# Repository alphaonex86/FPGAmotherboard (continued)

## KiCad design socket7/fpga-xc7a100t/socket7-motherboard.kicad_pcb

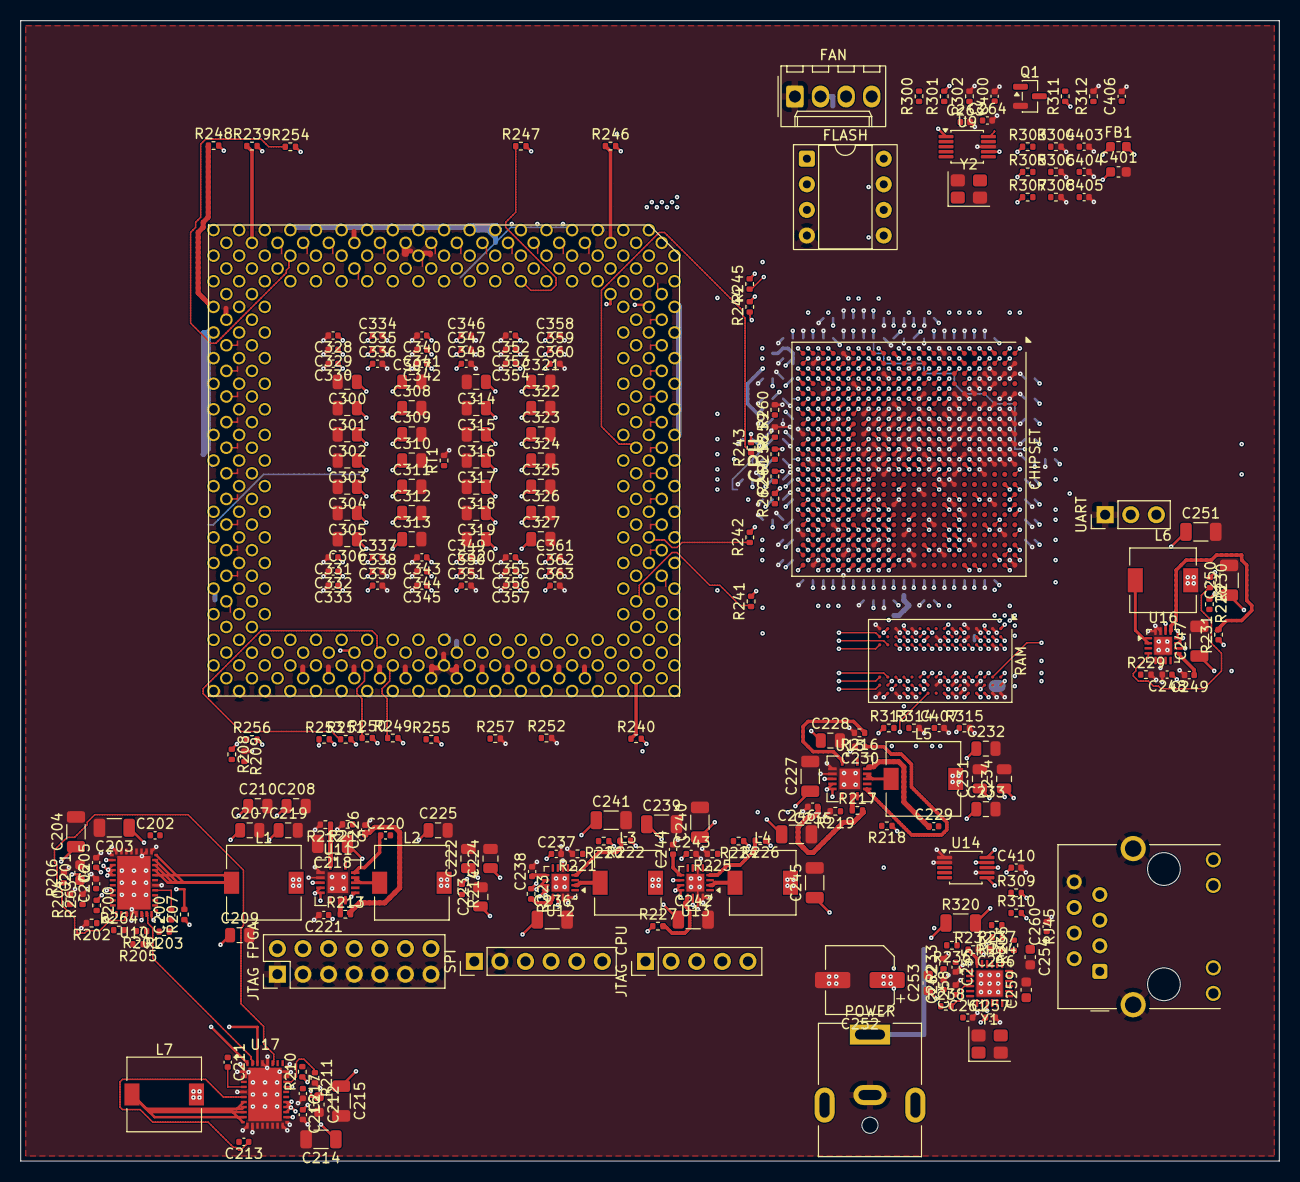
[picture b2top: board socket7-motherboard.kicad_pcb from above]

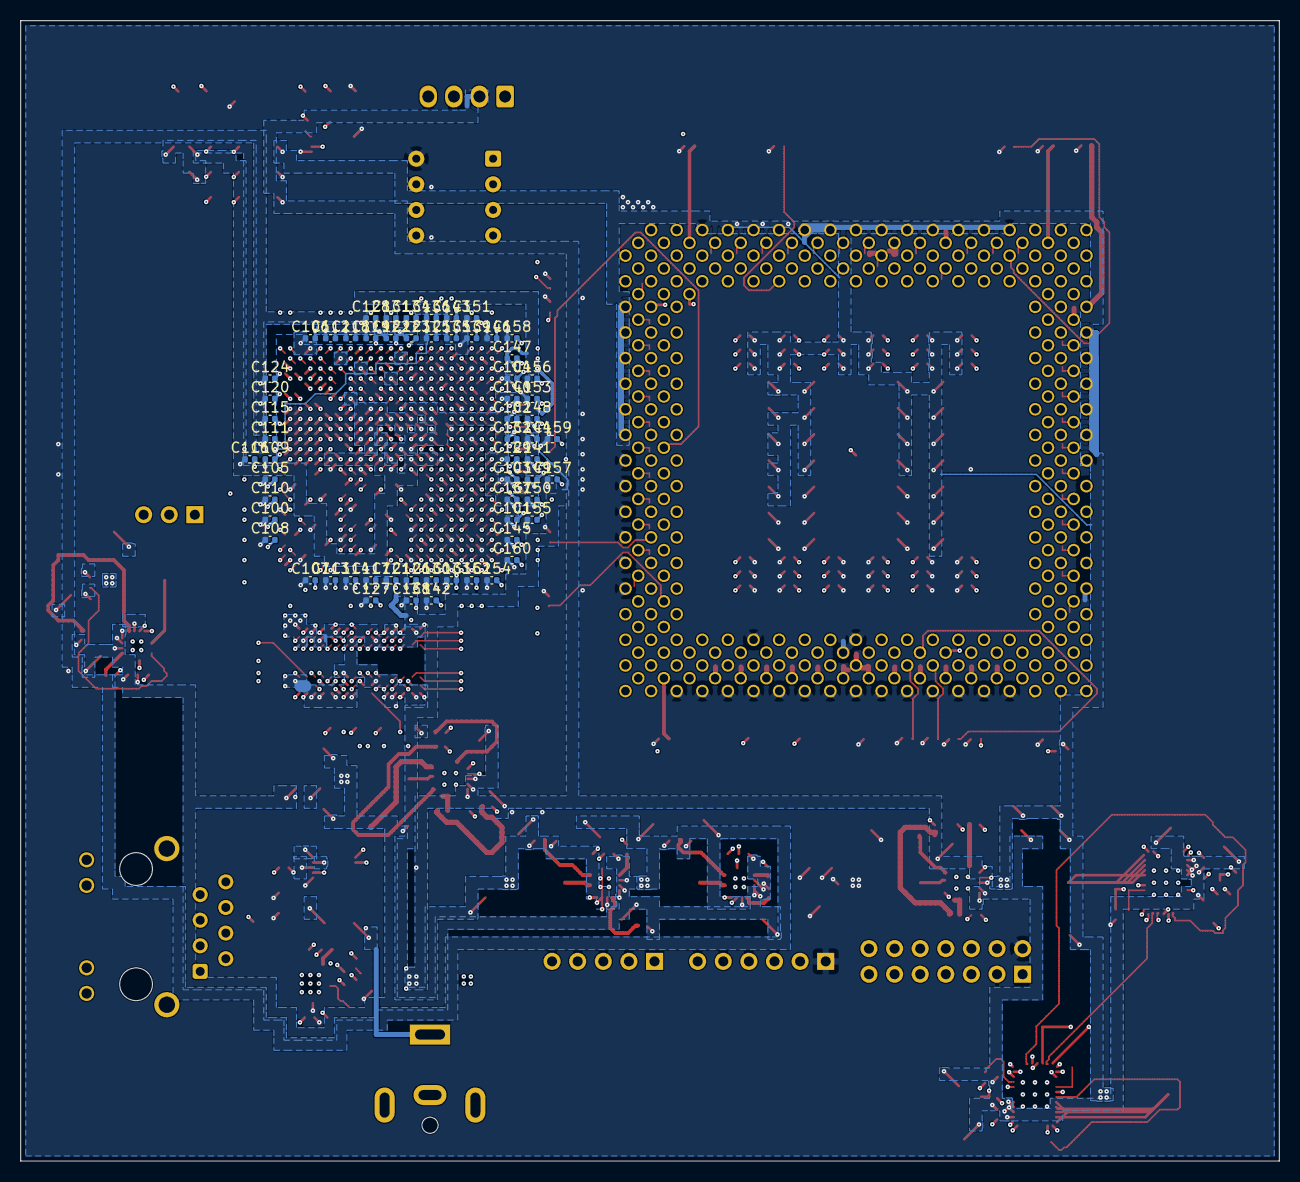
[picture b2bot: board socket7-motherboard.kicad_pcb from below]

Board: 8 copper layers, 124.8 x 113.1 mm, 313 parts (61 on the bottom side), 311 nets.

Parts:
C100, C101, C102, C103, C104, C105, C106, C107, C108, C109, C110, C111, C112, C113, C114, C115, C116, C117, C118, C119, C120, C121, C122, C123, C124, C125, C126, C127, C128, C129, C130, C131, C132, C133, C134, C135, C136, C137, C138, C139, C140, C141, C142, C143, C144, C145, C146, C147, C148, C149, C150, C151, C152, C153, C154, C155, C156, C157, C158, C159, C160: 470nF; C_0402_1005Metric
C200, C211: 1uF 16V X6S; C_0402_1005Metric
C201, C212: 4.7uF 16V X5R; C_0603_1608Metric
C202, C213: 100nF 16V X5R; C_0402_1005Metric
C203, C204, C214, C215, C218, C227, C236, C239, C240, C241, C242, C245, C246, C247, C250, C251: 22uF 25V X5R; C_1206_3216Metric
C205, C216, C221, C230, C403, C404, C405, C406: 10nF 50V X7R; C_0402_1005Metric
C206, C217: 1uF 25V X5R; C_0402_1005Metric
C207, C208, C209, C210, C222, C223, C224, C225: 47uF 6.3V X5R; C_0805_2012Metric
C219, C228: 4.7uF 25V X7R; C_0805_2012Metric
C220, C229, C237, C243, C248, C255, C256, C257, C260, C407, C410: 100nF 16V X7R; C_0402_1005Metric
C226, C235: 8.2nF 50V X7R; C_0402_1005Metric
C231, C232, C233, C234: 47uF 10V X5R; C_0805_2012Metric
C238, C244, C249: 3.3nF 50V X7R; C_0402_1005Metric
C252: 100uF 25V; CP_Elec_6.3x7.7
C253: 600R@100MHz bead; L_0603_1608Metric
C254: 10uF 10V X5R; C_0603_1608Metric
C258: 470pF 50V C0G; C_0402_1005Metric
C259: 1uF 16V X7R; C_0603_1608Metric
C261, C262: 15pF 50V C0G; C_0402_1005Metric
C263, C264: 4pF 50V C0G; C_0402_1005Metric
C300, C301, C302, C303, C304, C305, C306, C307, C308, C309, C310, C311, C312, C313, C314, C315, C316, C317, C318, C319, C320, C321, C322, C323, C324, C325, C326, C327: 22uF; C_0805_2012Metric
C328, C329, C330, C331, C332, C333, C334, C335, C336, C337, C338, C339, C340, C341, C342, C343, C344, C345, C346, C347, C348, C349, C350, C351, C352, C353, C354, C355, C356, C357, C358, C359, C360, C361, C362, C363: 100nF; C_0402_1005Metric
C400: 1nF 50V C0G; C_0402_1005Metric
C401: 470nF 50V X7R; C_0603_1608Metric
FB1: 600R@100MHz bead; L_0603_1608Metric
J1: HR911105A; RJ45_Hanrun_HR911105A_Horizontal
J2: SPI ISP; PinHeader_1x06_P2.54mm_Vertical
J3: PJ-063AH 12V; BarrelJack_CUI_PJ-063AH_Horizontal
J4: UART; PinHeader_1x03_P2.54mm_Vertical
J5: FPGA JTAG; PinHeader_2x07_P2.54mm_Vertical
J6: CPU JTAG; PinHeader_1x05_P2.54mm_Vertical
J7: fan 4-pin 1GND 2+12V 3TACH 4PWM; Molex_KK-254_AE-6410-04A_1x04_P2.54mm_Vertical
L1: VCC2 out; L_7.3x7.3_H4.5
L2: 3V3 out; L_7.3x7.3_H4.5
L3: 1V0 out; L_6.3x6.3_H3
L4: 1V8 out; L_6.3x6.3_H3
L5: 5V out; L_7.3x7.3_H4.5
L6: 1V35 out; L_6.3x6.3_H3
L7: VCC2 ph2 out; L_7.3x7.3_H4.5
Q1: BSS138; SOT-23
R200, R210: 10R 1%; R_0402_1005Metric
R201, R202, R205: 21.5k 1%; R_0402_1005Metric
R203: 110k 1%; R_0402_1005Metric
R204: 56.2k 1%; R_0402_1005Metric
R206: 4.64k 1%; R_0402_1005Metric
R207, R215, R219, R221, R225, R229, R233, R252, R257, R301, R302, R303, R305, R309, R310, R311: 10k 1%; R_0402_1005Metric
R208: 866R 1%; R_0402_1005Metric
R209: 0R; R_0402_1005Metric
R211: 17.8k 1%; R_0402_1005Metric
R212, R216, R222, R223, R226, R227, R230, R231: 100k 1%; R_0402_1005Metric
R213, R217, R300: 1.69k 1%; R_0402_1005Metric
R214: 31.6k 1%; R_0402_1005Metric
R218: 52.3k 1%; R_0402_1005Metric
R220, R308: 2.49k 1%; R_0402_1005Metric
R224: 12.4k 1%; R_0402_1005Metric
R228: 6.81k 1%; R_0402_1005Metric
R232: 12.1k 1%; R_0402_1005Metric
R234, R235, R236, R237: 49.9 1%; R_0402_1005Metric
R238, R263: 500R 1%; R_0402_1005Metric
R239, R248, R249, R251, R256: 8.2k 1%; R_0402_1005Metric
R240, R241, R242, R243, R244, R245, R246, R247, R250, R253, R254, R255: 4.7k 1%; R_0402_1005Metric
R258, R259, R260, R264, R313, R314: 1k 1%; R_0402_1005Metric
R261, R262, R304, R306, R312: 4.02k 1%; R_0402_1005Metric
R307: 30.9k 1%; R_0402_1005Metric
R315: 240R 1%; R_0402_1005Metric
R320: 10mR 1% 1W; R_1206_3216Metric
RT1: 10k NTC 1% B3380; R_0402_1005Metric
U2: XC7A100T-2FGG484I; Xilinx_FGG484
U3: MT41K128M16JT-125; FBGA-96_8x14mm_Layout9x16_P0.8mm
U7: LAN8720A-CP-TR; QFN-24-1EP_4x4mm_P0.5mm_EP2.6x2.6mm
U8: W25Q64JVDAIQ (DIP-8, socketed); DIP-8_W7.62mm_Socket
U9: SI5351A-B-GTR; MSOP-10_3x3mm_P0.5mm
U10: TPS546B24ARVFR VCC2; Texas_RVF0040A_LQFN-CLIP-40_5x7mm_P0.5mm
U11: TPS54620RGYR 3V3; Texas_S-PVQFN-N14
U12: TPS62130RGTR 1V0; QFN-16-1EP_3x3mm_P0.5mm_EP1.75x1.75mm
U13: TPS62130RGTR 1V8; QFN-16-1EP_3x3mm_P0.5mm_EP1.75x1.75mm
U14: INA226AIDGSR; MSOP-10_3x3mm_P0.5mm
U15: TPS54620RGYR 5V; Texas_S-PVQFN-N14
U16: TPS62130RGTR 1V35; QFN-16-1EP_3x3mm_P0.5mm_EP1.75x1.75mm
U17: TPS546B24ARVFR VCC2 ph2; Texas_RVF0040A_LQFN-CLIP-40_5x7mm_P0.5mm
XU1: Socket 7 ZIF 321p; Socket7_P55C_296
Y1, Y2: 25MHz; Crystal_SMD_3225-4Pin_3.2x2.5mm

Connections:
+1V0: C115.1, C119.1, C120.1, C123.1, C124.1, C128.1, C129.1, C131.1, C135.1, C137.1, C139.1, C140.1, C143.1, C147.1, C148.1, C149.1, C153.1, C239.1, C240.1, C241.1, L3.2, R220.1, R222.1, U2.H8, U2.H10, U2.J7, U2.J9, U2.J11, U2.K8, U2.L7, U2.L11, U2.M8, U2.N7, U2.N11, U2.P8, U2.P10, U2.R7, U2.R9, U2.T8, U2.T10, U12.14
+1V8: C109.1, C116.1, C126.1, C132.1, C141.1, C144.1, C245.1, C246.1, FB1.1, L4.2, R224.1, R226.1, U2.E12, U2.H12, U2.K12, U2.M12, U2.P12, U2.R11, U13.14
+1V8_ADC: C125.1, C401.1, FB1.2, U2.K10
+1V35: C106.1, C112.1, C118.1, C122.1, C134.1, C136.1, C250.1, C251.1, L6.2, R228.1, R230.1, R313.1, U2.C1, U2.F2, U2.H6, U2.J3, U2.M4, U2.N1, U3.A1, U3.A8, U3.B2, U3.C1, U3.C9, U3.D2, U3.D9, U3.E9, U3.F1, U3.G7, U3.H2, U3.H9, U3.K2, U3.K8, U3.N1, U3.N9, U3.R1, U3.R9, U16.14
+3V3: C100.1, C101.1, C102.1, C103.1, C104.1, C105.1, C107.1, C108.1, C110.1, C111.1, C113.1, C114.1, C117.1, C121.1, C127.1, C130.1, C133.1, C138.1, C142.1, C145.1, C146.1, C150.1, C151.1, C152.1, C154.1, C155.1, C156.1, C157.1, C158.1, C159.1, C160.1, C222.1, C223.1, C224.1, C225.1, C253.1, C257.1, C311.1, C312.1, C313.1, C318.1, C319.1, C320.1, C326.1, C327.1, C331.1, C332.1, C333.1, C337.1, C338.1, C339.1, C343.1, C344.1, C345.1, C349.1, C350.1, C351.1, C355.1, C356.1, C357.1, C361.1, C362.1, C363.1, C410.1, J2.1, J5.2, L2.2, R207.1, R214.1, R239.2, R240.2, R241.2, R242.2, R243.2, R244.2, R245.2, R246.2, R247.2, R248.2, R249.2, R250.2, R251.2, R253.2, R254.2, R255.2, R256.2, R258.2, R261.2, R262.2, R301.2, R305.1, R309.2, R310.2, R311.1, U2.A17, U2.AA7, U2.AA17, U2.AB4, U2.AB14, U2.B14, U2.C21, U2.D18, U2.E15, U2.F12, U2.F22, U2.G19, U2.H16, U2.J13, U2.K20, U2.L17, U2.M14, U2.N21, U2.P18, U2.R5, U2.R15, U2.T2, U2.T12, U2.T22, U2.U8, U2.U19, U2.U22, U2.V6, U2.V16, U2.W3, U2.W13, U2.Y10, U2.Y20, U7.9, U8.8, U9.1, U9.7, U14.6, XU1.A19 (VCC3), XU1.A21 (VCC3), XU1.A23 (VCC3), XU1.A25 (VCC3), XU1.A27 (VCC3), XU1.A29 (VCC3), XU1.AA37 (VCC3), XU1.AC37 (VCC3), XU1.AE37 (VCC3), XU1.AG37 (VCC3), XU1.AN21 (VCC3), XU1.AN23 (VCC3), XU1.AN25 (VCC3), XU1.AN27 (VCC3), XU1.AN29 (VCC3), XU1.E37 (VCC3), XU1.G37 (VCC3), XU1.J37 (VCC3), XU1.L33 (VCC3), XU1.L37 (VCC3), XU1.N37 (VCC3), XU1.Q37 (VCC3), XU1.S37 (VCC3), XU1.T34 (VCC3), XU1.U33 (VCC3), XU1.U37 (VCC3), XU1.W37 (VCC3), XU1.Y37 (VCC3)
+5V: C231.1, C232.1, C233.1, C234.1, C236.1, C237.1, C242.1, C243.1, C247.1, C248.1, L5.2, R218.1, R223.1, R227.1, R231.1, U12.10, U12.11, U12.12, U13.10, U13.11, U13.12, U16.10, U16.11, U16.12
+12V: C203.1, C204.1, C205.1, C214.1, C215.1, C216.1, C218.1, C219.1, C227.1, C228.1, C252.1, J7.2, R200.1, R210.1, R307.1, R320.2, U10.22, U10.23, U10.24, U10.25, U11.4, U11.5, U11.6, U14.8, U14.9, U15.4, U15.5, U15.6, U17.22, U17.23, U17.24, U17.25
+12V_IN: J3.1, R320.1, U14.10
GND: C100.2, C101.2, C102.2, C103.2, C104.2, C105.2, C106.2, C107.2, C108.2, C109.2, C110.2, C111.2, C112.2, C113.2, C114.2, C115.2, C116.2, C117.2, C118.2, C119.2, C120.2, C121.2, C122.2, C123.2, C124.2, C125.2, C126.2, C127.2, C128.2, C129.2, C130.2, C131.2, C132.2, C133.2, C134.2, C135.2, C136.2, C137.2, C138.2, C139.2, C140.2, C141.2, C142.2, C143.2, C144.2, C145.2, C146.2, C147.2, C148.2, C149.2, C150.2, C151.2, C152.2, C153.2, C154.2, C155.2, C156.2, C157.2, C158.2, C159.2, C160.2, C201.2, C203.2, C204.2, C205.2, C206.2, C207.2, C208.2, C209.2, C210.2, C212.2, C214.2, C215.2, C216.2, C217.2, C218.2, C219.2, C221.2, C222.2, C223.2, C224.2, C225.2, C226.2, C227.2, C228.2, C230.2, C231.2, C232.2, C233.2, C234.2, C235.2, C236.2, C237.2, C238.2, C239.2, C240.2, C241.2, C242.2, C243.2, C244.2, C245.2, C246.2, C247.2, C248.2, C249.2, C250.2, C251.2, C252.2, C254.2, C255.2, C256.2, C257.2, C258.2, C259.2, C260.2, C261.2, C262.2, C263.2, C264.2, C300.2, C301.2, C302.2, C303.2, C304.2, C305.2, C306.2, C307.2, C308.2, C309.2, C310.2, C311.2, C312.2, C313.2, C314.2, C315.2, C316.2, C317.2, C318.2, C319.2, C320.2, C321.2, C322.2, C323.2, C324.2, C325.2, C326.2, C327.2, C328.2, C329.2, C330.2, C331.2, C332.2, C333.2, C334.2, C335.2, C336.2, C337.2, C338.2, C339.2, C340.2, C341.2, C342.2, C343.2, C344.2, C345.2, C346.2, C347.2, C348.2, C349.2, C350.2, C351.2, C352.2, C353.2, C354.2, C355.2, C356.2, C357.2, C358.2, C359.2, C360.2, C361.2, C362.2, C363.2, C400.2, C401.2, C403.2, C404.2, C405.2, C406.2, C407.2, C410.2, J1.8, J1.SH, J2.2, J3.2, J4.1, J5.1, J5.3, J5.5, J5.7, J5.9, J5.11, J5.13, J7.1, Q1.2, R202.2, R204.2, R206.2, R209.1, R211.2, R212.2, R215.2, R216.2, R219.2, R221.2, R225.2, R229.2, R232.2, R233.2, R252.2, R257.2, R259.2, R260.2, R263.2, R302.2, R304.2, R306.2, R308.2, R312.2, R314.2, R315.2, RT1.2, U2.A2, U2.A3, U2.A5, U2.A7, U2.A8, U2.A9, U2.A10, U2.A11, U2.A12, U2.A22, U2.AA2, U2.AA12, U2.AA22, U2.AB9, U2.AB19, U2.B3, U2.B5, U2.B7, U2.B8, U2.B9, U2.B10, U2.B11, U2.B12, U2.B19, U2.C3, U2.C4, U2.C6, U2.C8, U2.C9, U2.C10, U2.C11, U2.C12, U2.C16, U2.D3, U2.D4, U2.D6, U2.D8, U2.D9, U2.D10, U2.D11, U2.D12, U2.D13, U2.E4, U2.E5, U2.E7, U2.E8, U2.E9, U2.E11, U2.E20, U2.F5, U2.F7, U2.F8, U2.F9, U2.F11, U2.F17, U2.G5, U2.G6, U2.G7, U2.G8, U2.G9, U2.G10, U2.G12, U2.G13, U2.G14, U2.G16, U2.H1, U2.H7, U2.H9, U2.H11, U2.H14, U2.H21, U2.J8, U2.J10, U2.J12, U2.J18, U2.K5, U2.K7, U2.K9, U2.K11, U2.K15, U2.L2, U2.L8, U2.L9, U2.L10, U2.L21, U2.L22, U2.M7, U2.M9, U2.M10, U2.M11, U2.M19, U2.N6, U2.N8, U2.N16, U2.P3, U2.P7, U2.P9, U2.P11, U2.P13, U2.R8, U2.R10, U2.R12, U2.R20, U2.T7, U2.T9, U2.T11, U2.T17, U2.U4, U2.U14, U2.V1, U2.V11, U2.V21, U2.W8, U2.W18, U2.Y5, U2.Y15, U3.A9, U3.B1, U3.B3, U3.B9, U3.D1, U3.D8, U3.E1, U3.E2, U3.E8, U3.F9, U3.G1, U3.G8, U3.G9, U3.J2, U3.J8, U3.M1, U3.M9, U3.P1, U3.P9, U3.T1, U3.T9, U7.25, U8.4, U9.8, U10.6, U10.13, U10.14, U10.15, U10.16, U10.17, U10.18, U10.19, U10.20, U10.21, U10.36, U10.37, U10.41, U11.2, U11.3, U11.15, U12.6, U12.15, U12.16, U12.17, U13.6, U13.15, U13.16, U13.17, U14.1, U14.2, U14.7, U15.2, U15.3, U15.15, U16.6, U16.15, U16.16, U16.17, U17.1, U17.2, U17.3, U17.6, U17.13, U17.14, U17.15, U17.16, U17.17, U17.18, U17.19, U17.20, U17.21, U17.30, U17.31, U17.32, U17.36, U17.37, U17.41, XU1.AB02 (VSS), XU1.AB04 (HOLD), XU1.AB36 (VSS), XU1.AD02 (VSS), XU1.AD36 (VSS), XU1.AF02 (VSS), XU1.AF36 (VSS), XU1.AH02 (VSS), XU1.AJ37 (VSS), XU1.AL37 (VSS), XU1.AM08 (VSS), XU1.AM10 (VSS), XU1.AM12 (VSS), XU1.AM14 (VSS), XU1.AM16 (VSS), XU1.AM18 (VSS), XU1.AM20 (VSS), XU1.AM22 (VSS), XU1.AM24 (VSS), XU1.AM26 (VSS), XU1.AM28 (VSS), XU1.AM30 (VSS), XU1.AN37 (VSS), XU1.B06 (VSS), XU1.B08 (VSS), XU1.B10 (VSS), XU1.B12 (VSS), XU1.B14 (VSS), XU1.B16 (VSS), XU1.B18 (VSS), XU1.B20 (VSS), XU1.B22 (VSS), XU1.B24 (VSS), XU1.B26 (VSS), XU1.B28 (VSS), XU1.H02 (VSS), XU1.H36 (VSS), XU1.K02 (VSS), XU1.K36 (VSS), XU1.M02 (VSS), XU1.M36 (VSS), XU1.P02 (VSS), XU1.P36 (VSS), XU1.R02 (VSS), XU1.R36 (VSS), XU1.T02 (VSS), XU1.T36 (VSS), XU1.U35 (VSS), XU1.V02 (VSS), XU1.V36 (VSS), XU1.W03 (EWBE#), XU1.X02 (VSS), XU1.X36 (VSS), XU1.Z02 (VSS), XU1.Z36 (VSS), Y1.2, Y1.4, Y2.2, Y2.4
VCC2: C207.1, C208.1, C209.1, C210.1, C300.1, C301.1, C302.1, C303.1, C304.1, C305.1, C306.1, C307.1, C308.1, C309.1, C310.1, C314.1, C315.1, C316.1, C317.1, C321.1, C322.1, C323.1, C324.1, C325.1, C328.1, C329.1, C330.1, C334.1, C335.1, C336.1, C340.1, C341.1, C342.1, C346.1, C347.1, C348.1, C352.1, C353.1, C354.1, C358.1, C359.1, C360.1, L1.2, L7.2, R208.1, R303.1, XU1.A07 (VCC2), XU1.A09 (VCC2), XU1.A11 (VCC2), XU1.A13 (VCC2), XU1.A15 (VCC2), XU1.A17 (VCC2), XU1.AA01 (VCC2), XU1.AC01 (VCC2), XU1.AE01 (VCC2), XU1.AG01 (VCC2), XU1.AN09 (VCC2), XU1.AN11 (VCC2), XU1.AN13 (VCC2), XU1.AN15 (VCC2), XU1.AN17 (VCC2), XU1.AN19 (VCC2), XU1.G01 (VCC2), XU1.J01 (VCC2), XU1.L01 (VCC2), XU1.N01 (VCC2), XU1.Q01 (VCC2), XU1.S01 (VCC2), XU1.U01 (VCC2), XU1.W01 (VCC2), XU1.Y01 (VCC2)
cpu_a20m_n: U2.U6, XU1.AK08 (A20M#)
cpu_a[3]: U2.W19, XU1.AL35 (A3)
cpu_a[4]: U2.Y18, XU1.AM34 (A4)
cpu_a[5]: U2.T16, XU1.AK32 (A5)
cpu_a[6]: U2.AB17, XU1.AN33 (A6)
cpu_a[7]: U2.Y17, XU1.AL33 (A7)
cpu_a[8]: U2.U16, XU1.AM32 (A8)
cpu_a[9]: U2.T15, XU1.AK30 (A9)
cpu_a[10]: U2.AA16, XU1.AN31 (A10)
cpu_a[11]: U2.Y16, XU1.AL31 (A11)
cpu_a[12]: U2.V15, XU1.AL29 (A12)
cpu_a[13]: U2.AA15, XU1.AK28 (A13)
cpu_a[14]: U2.V14, XU1.AL27 (A14)
cpu_a[15]: U2.W14, XU1.AK26 (A15)
cpu_a[16]: U2.AA14, XU1.AL25 (A16)
cpu_a[17]: U2.Y13, XU1.AK24 (A17)
cpu_a[18]: U2.AB13, XU1.AL23 (A18)
cpu_a[19]: U2.Y12, XU1.AK22 (A19)
cpu_a[20]: U2.W11, XU1.AL21 (A20)
cpu_a[21]: U2.T18, XU1.AF34 (A21)
cpu_a[22]: U2.AA21, XU1.AH36 (A22)
cpu_a[23]: U2.U17, XU1.AE33 (A23)
cpu_a[24]: U2.AA20, XU1.AG35 (A24)
cpu_a[25]: U2.AB20, XU1.AJ35 (A25)
cpu_a[26]: U2.U18, XU1.AH34 (A26)
cpu_a[27]: U2.V17, XU1.AG33 (A27)
cpu_a[28]: U2.AB21, XU1.AK36 (A28)
cpu_a[29]: U2.V18, XU1.AK34 (A29)
cpu_a[30]: U2.AB11, XU1.AM36 (A30)
cpu_a[31]: U2.W17, XU1.AJ33 (A31)
cpu_ads_n: U2.AB12, XU1.AJ05 (ADS#)
cpu_ahold: U2.Y3, XU1.V04 (AHOLD)
cpu_ap: R239.1, XU1.AK02 (AP)
cpu_be[0]: U2.AA3, XU1.AL09 (BE0#)
cpu_be[1]: U2.Y7, XU1.AK10 (BE1#)
cpu_be[2]: U2.U7, XU1.AL11 (BE2#)
cpu_be[3]: U2.V4, XU1.AK12 (BE3#)
cpu_be[4]: U2.V8, XU1.AL13 (BE4#)
cpu_be[5]: U2.Y19, XU1.AK14 (BE5#)
cpu_be[6]: U2.V9, XU1.AL15 (BE6#)
cpu_be[7]: U2.AA10, XU1.AK16 (BE7#)
cpu_bf[0]: U2.AB18, XU1.Y33 ([BF0])
cpu_bf[1]: U2.V19, XU1.X34 ([BF1])
cpu_boff_n: U2.R2, XU1.Z04 (BOFF#)
cpu_brdy_n: U2.R6, XU1.X04 (BRDY#)
cpu_cache_n: U2.Y1, XU1.U03 (CACHE#)
cpu_clk: U9.10, XU1.AK18 (CLK)
cpu_d[0]: U2.W20, XU1.K34 (D0)
cpu_d[1]: U2.R18, XU1.G35 (D1)
cpu_d[2]: U2.Y21, XU1.J35 (D2)
cpu_d[3]: U2.AA19, XU1.G33 (D3)
cpu_d[4]: U2.W22, XU1.F36 (D4)
cpu_d[5]: U2.V20, XU1.F34 (D5)
cpu_d[6]: U2.U21, XU1.E35 (D6)
cpu_d[7]: U2.R16, XU1.E33 (D7)
cpu_d[8]: U2.U20, XU1.D34 (D8)
cpu_d[9]: U2.N22, XU1.C37 (D9)
cpu_d[10]: U2.T21, XU1.C35 (D10)
cpu_d[11]: U2.V22, XU1.B36 (D11)
cpu_d[12]: U2.N17, XU1.D32 (D12)
cpu_d[13]: U2.T20, XU1.B34 (D13)
cpu_d[14]: U2.P19, XU1.C33 (D14)
cpu_d[15]: U2.Y22, XU1.A35 (D15)
cpu_d[16]: U2.AA18, XU1.B32 (D16)
cpu_d[17]: U2.Y9, XU1.C31 (D17)
cpu_d[18]: U2.R19, XU1.A33 (D18)
cpu_d[19]: U2.U15, XU1.D28 (D19)
cpu_d[20]: U2.W16, XU1.B30 (D20)
cpu_d[21]: U2.AB16, XU1.C29 (D21)
cpu_d[22]: U2.P16, XU1.A31 (D22)
cpu_d[23]: U2.AB15, XU1.D26 (D23)
cpu_d[24]: U2.W15, XU1.C27 (D24)
cpu_d[25]: U2.V13, XU1.C23 (D25)
cpu_d[26]: U2.Y14, XU1.D24 (D26)
cpu_d[27]: U2.W12, XU1.C21 (D27)
cpu_d[28]: U2.AA13, XU1.D22 (D28)
cpu_d[29]: U2.Y11, XU1.C19 (D29)
cpu_d[30]: U2.T3, XU1.D20 (D30)
cpu_d[31]: U2.P20, XU1.C17 (D31)
cpu_d[32]: U2.W10, XU1.C15 (D32)
cpu_d[33]: U2.V10, XU1.D16 (D33)
cpu_d[34]: U2.W9, XU1.C13 (D34)
cpu_d[35]: U2.AB10, XU1.D14 (D35)
cpu_d[36]: U2.Y8, XU1.C11 (D36)
cpu_d[37]: U2.AA9, XU1.D12 (D37)
cpu_d[38]: U2.V7, XU1.C09 (D38)
cpu_d[39]: U2.AB8, XU1.D10 (D39)
cpu_d[40]: U2.AB7, XU1.D08 (D40)
cpu_d[41]: U2.T1, XU1.A05 (D41)
cpu_d[42]: U2.W7, XU1.E09 (D42)
cpu_d[43]: U2.R17, XU1.B04 (D43)
cpu_d[44]: U2.W6, XU1.D06 (D44)
cpu_d[45]: U2.AA6, XU1.C05 (D45)
cpu_d[46]: U2.T6, XU1.E07 (D46)
cpu_d[47]: U2.AB3, XU1.C03 (D47)
cpu_d[48]: U2.T4, XU1.D04 (D48)
cpu_d[49]: U2.AB6, XU1.E05 (D49)
cpu_d[50]: U2.AA1, XU1.D02 (D50)
cpu_d[51]: U2.W4, XU1.F04 (D51)
cpu_d[52]: U2.U2, XU1.E03 (D52)
cpu_d[53]: U2.T5, XU1.G05 (D53)
cpu_d[54]: U2.AB1, XU1.E01 (D54)
cpu_d[55]: U2.V2, XU1.G03 (D55)
cpu_d[56]: U2.Y4, XU1.H04 (D56)
cpu_d[57]: U2.W2, XU1.J03 (D57)
cpu_d[58]: U2.U5, XU1.J05 (D58)
cpu_d[59]: U2.AA4, XU1.K04 (D59)
cpu_d[60]: U2.U3, XU1.L05 (D60)
cpu_d[61]: U2.Y2, XU1.L03 (D61)
cpu_d[62]: U2.R3, XU1.M04 (D62)
cpu_d[63]: U2.Y6, XU1.N03 (D63)
cpu_dc_n: U2.U1, XU1.AK04 (D/C#)
cpu_dp[0]: R240.1, XU1.D36 (DP0)
cpu_dp[1]: R241.1, XU1.D30 (DP1)
cpu_dp[2]: R242.1, XU1.C25 (DP2)
cpu_dp[3]: R243.1, XU1.D18 (DP3)
cpu_dp[4]: R244.1, XU1.C07 (DP4)
cpu_dp[5]: R245.1, XU1.F06 (DP5)
cpu_dp[6]: R246.1, XU1.F02 (DP6)
cpu_dp[7]: R247.1, XU1.N05 (DP7)
cpu_eads_n: U2.W1, XU1.AM04 (EADS#)
cpu_flush_n: R248.1, XU1.AN07 (FLUSH#)
cpu_frcmc_n: R249.1, XU1.Y35 (FRCMC#1)
cpu_hitm_n: U2.V5, XU1.AL05 (HITM#)
cpu_ignne_n: R250.1, XU1.AA35 (IGNNE#)
cpu_init: U2.P17, XU1.AA33 (INIT)
cpu_intr: U2.W21, XU1.AD34 (INTR/LINT0)
cpu_ken_inv_n: U2.AA5, XU1.U05 (INV), XU1.W05 (KEN#)
cpu_lock_n: U2.AB2, XU1.AH04 (LOCK#)
cpu_mio_n: U2.V3, XU1.T04 (M/IO#)
cpu_na_n: U2.R4, XU1.Y05 (NA#)
cpu_nmi: U2.AB5, XU1.AC33 (NMI/LINT1)
cpu_pen_n: R251.1, XU1.Z34 (PEN#)
cpu_picd1: R252.1, XU1.L35 (PICD1)
cpu_reset: R256.1, U2.AA11, XU1.AK20 (RESET)
cpu_smi_n: R253.1, XU1.AB34 (SMI#)
cpu_smiact_n: R254.1, XU1.AG03 (SMIACT#)
cpu_stpclk_n: R255.1, U2.T14, XU1.V34 (STPCLK#)
cpu_tck: J6.1, XU1.M34 (TCK)
cpu_tdi: J6.3, XU1.N35 (TDI)
cpu_tdo: J6.4, XU1.N33 (TDO)
cpu_tms: J6.2, XU1.P34 (TMS)
cpu_trst_n: J6.5, R257.1, XU1.Q33 (TRST#)
cpu_wbwt_n: U2.AA8, XU1.AA05 (WB/WT#)
cpu_wr_n: U2.W5, XU1.AM06 (W/R#)
ddr3_a[0]: U2.M2, U3.N3
ddr3_a[1]: U2.M5, U3.P7
ddr3_a[2]: U2.M3, U3.P3
ddr3_a[3]: U2.M1, U3.N2
ddr3_a[4]: U2.L6, U3.P8
ddr3_a[5]: U2.P1, U3.P2
ddr3_a[6]: U2.N3, U3.R8
ddr3_a[7]: U2.N2, U3.R2
ddr3_a[8]: U2.M6, U3.T8
ddr3_a[9]: U2.R1, U3.R3
ddr3_a[10]: U2.L5, U3.L7
ddr3_a[11]: U2.N5, U3.R7
ddr3_a[12]: U2.N4, U3.N7
ddr3_a[13]: U2.P2, U3.T3
ddr3_a[14]: U2.P6, U3.T7
ddr3_ba[0]: U2.L3, U3.M2
ddr3_ba[1]: U2.K6, U3.N8
ddr3_ba[2]: U2.L4, U3.M3
ddr3_cas_n: U2.K3, U3.K3
ddr3_ck_n: U2.P4, U3.K7
ddr3_ck_p: U2.P5, U3.J7
ddr3_cke: U2.J6, U3.K9
ddr3_cs_n: U2.F4, U3.L2
ddr3_dm[0]: U2.G3, U3.E7
ddr3_dm[1]: U2.F1, U3.D3
ddr3_dq[0]: U2.G2, U3.E3
ddr3_dq[1]: U2.H4, U3.F7
ddr3_dq[2]: U2.H5, U3.F2
ddr3_dq[3]: U2.J1, U3.F8
ddr3_dq[4]: U2.K1, U3.H3
ddr3_dq[5]: U2.H3, U3.H8
ddr3_dq[6]: U2.H2, U3.G2
ddr3_dq[7]: U2.J5, U3.H7
ddr3_dq[8]: U2.E3, U3.D7
ddr3_dq[9]: U2.B2, U3.C3
ddr3_dq[10]: U2.F3, U3.C8
ddr3_dq[11]: U2.D2, U3.C2
ddr3_dq[12]: U2.C2, U3.A7
ddr3_dq[13]: U2.A1, U3.A2
ddr3_dq[14]: U2.E2, U3.B8
ddr3_dq[15]: U2.B1, U3.A3
ddr3_dqs_n[0]: U2.J2, U3.G3
ddr3_dqs_n[1]: U2.D1, U3.B7
ddr3_dqs_p[0]: U2.K2, U3.F3
ddr3_dqs_p[1]: U2.E1, U3.C7
ddr3_odt: U2.K4, U3.K1
ddr3_ras_n: U2.J4, U3.J3
ddr3_reset_n: U2.G1, U3.T2
ddr3_vref: C407.1, R313.2, R314.1, U3.H1, U3.M8
ddr3_we_n: U2.L1, U3.L3
ddr3_zq: R315.1, U3.L8
en_vcc2: R263.1, U2.AB22, U10.27, U17.27
eth_mdc: U2.A19, U7.13
eth_mdi_rxn: J1.6, R237.1, U7.22
eth_mdi_rxp: J1.3, R236.1, U7.23
eth_mdi_txn: J1.2, R235.1, U7.20
eth_mdi_txp: J1.1, R234.1, U7.21
eth_mdio: U2.B22, U7.12
eth_nintsel: R233.1, U7.2
eth_rbias: R232.1, U7.24
eth_ref_clk: U2.C18, U7.14
eth_rmii_crs_dv: U2.A21, U7.11
eth_rmii_rx_er: U2.B21, U7.10
eth_rmii_rxd[0]: U2.A20, U7.8
eth_rmii_rxd[1]: U2.E22, U7.7
eth_rmii_tx_en: U2.A15, U7.16
eth_rmii_txd[0]: U2.A14, U7.17
eth_rmii_txd[1]: U2.A13, U7.18
eth_rst_n: U2.A16, U7.15
eth_vdda: C253.2, C254.1, C255.1, C256.1, C260.1, J1.4, J1.5, R234.2, R235.2, R236.2, R237.2, U7.1, U7.19
eth_vddcr: C258.1, C259.1, U7.6
eth_xtal1: C261.1, U7.5, Y1.1
eth_xtal2: C262.1, R238.1, Y1.3
eth_xtal2_drv: R238.2, U7.4
fan_pwm: J7.4, Q1.3
fan_pwm_g: Q1.1, R302.1, U2.G17
fan_tach: J7.3, R300.1, R301.1
fan_tach_f: C400.1, R300.2, U2.G18
fpga_init_b: R262.1, U2.U12
fpga_m0: R258.1, U2.U11
fpga_m1: R259.1, U2.U10
fpga_m2: R260.1, U2.U9
fpga_program_b: R261.1, U2.N12
fpga_refclk: U2.K18, U9.9
i2c_scl: R309.1, U2.H18, U9.4, U10.3, U14.5
i2c_sda: R310.1, U2.G20, U9.5, U10.2, U14.4
jtag_tck: J5.6, U2.V12
jtag_tdi: J5.10, U2.R13
jtag_tdo: J5.8, U2.U13
jtag_tms: J5.4, U2.T13
spi_clk: J2.4, U2.L12, U8.6
spi_cs_n: J2.3, U2.T19, U8.1
spi_dq0: J2.6, U2.P22, U8.5
spi_dq1: J2.5, U2.R22, U8.2
spi_dq2: U2.P21, U8.3
spi_dq3: U2.R21, U8.7
sw_1v0: L3.1, U12.1, U12.2, U12.3
sw_1v8: L4.1, U13.1, U13.2, U13.3
sw_1v35: L6.1, U16.1, U16.2, U16.3
sw_3v3: C220.2, L2.1, U11.11, U11.12
sw_5v: C229.2, L5.1, U15.11, U15.12
sw_vcc2: C202.2, L1.1, U10.8, U10.9, U10.10, U10.11, U10.12
sw_vcc2_b: C213.2, L7.1, U17.8, U17.9, U17.10, U17.11, U17.12
tsen_socket: C406.1, R311.2, R312.1, RT1.1, U2.G15
u9_xa: C263.1, U9.2, Y2.1
u9_xb: C264.1, U9.3, Y2.3
u10_avin: C206.1, R200.2, U10.26
u10_boot: C202.1, U10.7
u10_bp1v5: C200.1, R201.1, R203.1, R205.1, U10.4
u10_drtn: C200.2, U10.5
u10_msel1: R201.2, R202.1, U10.32
u10_msel2: R203.2, R204.1, U10.29
u10_pgood: R207.2, U10.1
u10_vdd5: C201.1, U10.28
u10_vsel: R205.2, R206.1, U10.30
u11_boot: C220.1, U11.13
u11_comp: R213.1, U11.8
u11_compz: C226.1, R213.2
u11_fb: R214.2, R215.1, U11.7
u11_rt: R212.1, U11.1
u11_ss: C221.1, U11.9
u12_en: R223.2, U12.13
u12_fb: R220.2, R221.1, U12.5
u12_pg: R222.2, U12.4
u12_ss: C238.1, U12.9
u13_en: R227.2, U13.13
u13_fb: R224.2, R225.1, U13.5
u13_pg: R226.2, U13.4
u13_ss: C244.1, U13.9
u15_boot: C229.1, U15.13
u15_comp: R217.1, U15.8
u15_compz: C235.1, R217.2
u15_fb: R218.2, R219.1, U15.7
u15_rt: R216.1, U15.1
u15_ss: C230.1, U15.9
u16_en: R231.2, U16.13
u16_fb: R228.2, R229.1, U16.5
u16_pg: R230.2, U16.4
u16_ss: C249.1, U16.9
u17_avin: C217.1, R210.2, U17.26
u17_boot: C213.1, U17.7
u17_bp1v5: C211.1, U17.4, U17.34
u17_drtn: C211.2, U17.5
u17_msel2: R211.1, U17.29
u17_vdd5: C212.1, U17.28
uart_rx: J4.2, U2.H19
uart_tx: J4.3, U2.H20
vcc2_bcx_clk: U10.39, U17.39
vcc2_bcx_dat: U10.40, U17.40
vcc2_gsense: R209.2, R264.2, U10.34
vcc2_sense: R208.2, R264.1, U10.33
vcc2_sync: U10.38, U17.38
vcc2_vshare: U10.35, U17.35
vsen_3v3: C404.1, R305.2, R306.1, U2.J14
vsen_12v: C405.1, R307.2, R308.1, U2.M21
vsen_vcc2: C403.1, R303.2, R304.1, U2.H13
